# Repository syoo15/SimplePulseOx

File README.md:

# SimplePulseOx

## Eagle CAD schematic for Pulse Oximter using red LED
### UIUC project during BIOE 415 class

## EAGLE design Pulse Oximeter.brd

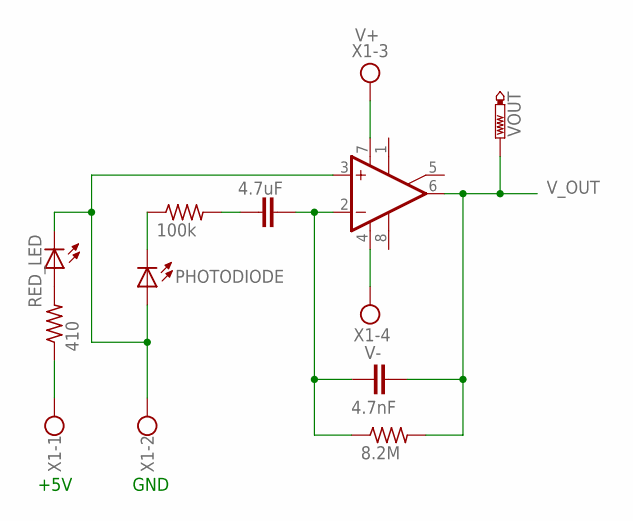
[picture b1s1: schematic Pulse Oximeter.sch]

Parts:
C1: 4.7uF; C2.5-3
C2: 4.7nF; C2.5-3
IC1: LM741P; DIL08
PHOTODIODE: LED_ELD260; LED_LD260
R1: 100k; 0204/5
R2: 8.2M; 0204/5
R3: 410; 0204/5
RED_LED: LED_ELD260; LED_LD260
VOUT: PTR1PAD1-13; P1-13
X1: W237-4

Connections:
unnamed: R3.1, X1.1
unnamed: IC1.3 (+IN), PHOTODIODE.A, RED_LED.K (C), X1.2
unnamed: C1.2, C2.1, IC1.2 (-IN), R2.1
unnamed: C1.1, R1.2
unnamed: PHOTODIODE.K (C), R1.1
unnamed: R3.2, RED_LED.A
V+: IC1.7 (V+), X1.3
V-: IC1.4 (V-), X1.4
V_OUT: C2.2, IC1.6 (OUT), R2.2, VOUT.TP

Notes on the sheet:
+5V
GND

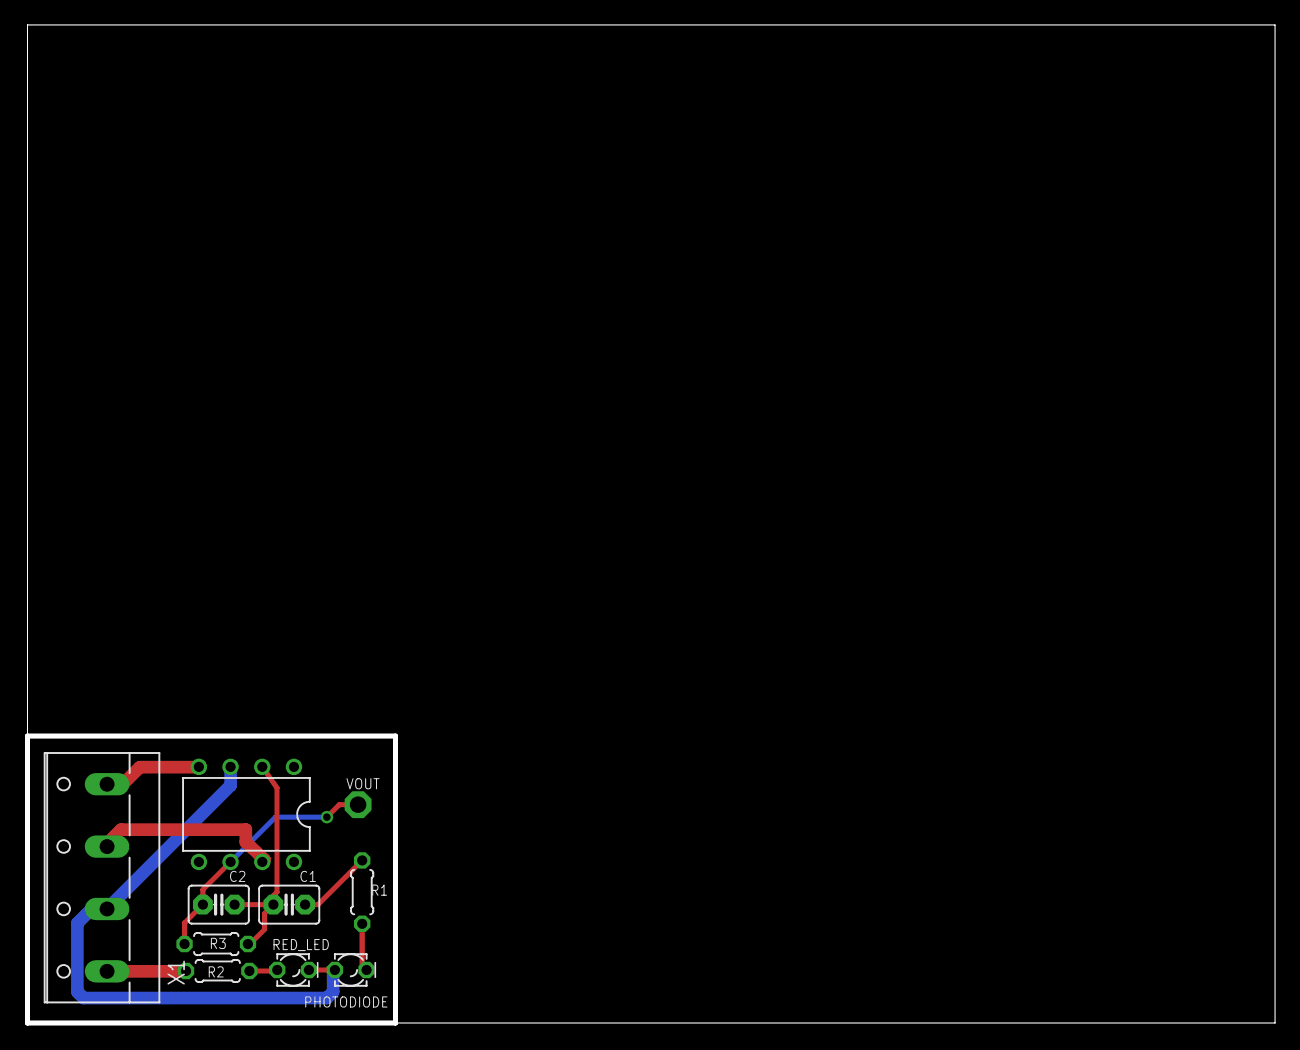
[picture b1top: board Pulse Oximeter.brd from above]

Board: 2 copper layers, 100.0 x 80.0 mm, 10 parts (0 on the bottom side), 9 nets.

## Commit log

2017-02-12 First commit
    EagleCAD schematic for simple Pulse Oximeter contributed by Arnav Gulati and Seokchan Yoo
